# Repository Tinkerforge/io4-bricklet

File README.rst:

IO-4 Bricklet
=============

This repository contains the firmware source code and the hardware design
files. The documentation generator configs can be found at
https://github.com/Tinkerforge/generators

Repository Content
------------------

software/:
 * examples/: Examples for all supported languages
 * build/: Compiled files
 * src/: Source code of firmware
 * Makefile: Makefile to build project

hardware/:
 * Contains KiCad project files and additionally schematics as PDF

datasheets/:
 * Contains datasheets for sensors and complex ICs that are used

Hardware
--------

The hardware is designed with the open source EDA Suite KiCad
(http://www.kicad.org). Before you are able to open the files,
you have to install the Tinkerforge kicad-libraries
(https://github.com/Tinkerforge/kicad-libraries). You can either clone
them directly in hardware/ or clone them in a separate folder and
symlink them into hardware/
(ln -s kicad_path/kicad-libraries project_path/hardware). After that you
can open the .pro file in hardware/ with KiCad and from there view and
modify the schematics and the PCB layout.

Software
--------

If you want to do your own Brick/Bricklet firmware development we highly
recommend that you use our build environment setup script and read the
tutorial (https://www.tinkerforge.com/en/doc/Tutorials/Tutorial_Build_Environment/Tutorial.html).

To compile the C code we recommend you to install the newest GNU Arm Embedded
Toolchain (https://launchpad.net/gcc-arm-embedded/+download).
You also need to install bricklib (https://github.com/Tinkerforge/bricklib)
and brickletlib (https://github.com/Tinkerforge/brickletlib).

You can either clone it directly in software/src/ or clone it in a
separate folder and symlink it into software/src/
(ln -s bricklib_path/bricklib project_path/software/src/ and
ln -s brickletlib_path/brickletlib project_path/software/src/).
Finally make sure to have CMake installed
(http://www.cmake.org/cmake/resources/software.html).

After that you can build the firmware by invoking make in software/.
The firmware (.bin) can then be found in software/build/ and uploaded
with brickv (click button "Flashing" on start screen).

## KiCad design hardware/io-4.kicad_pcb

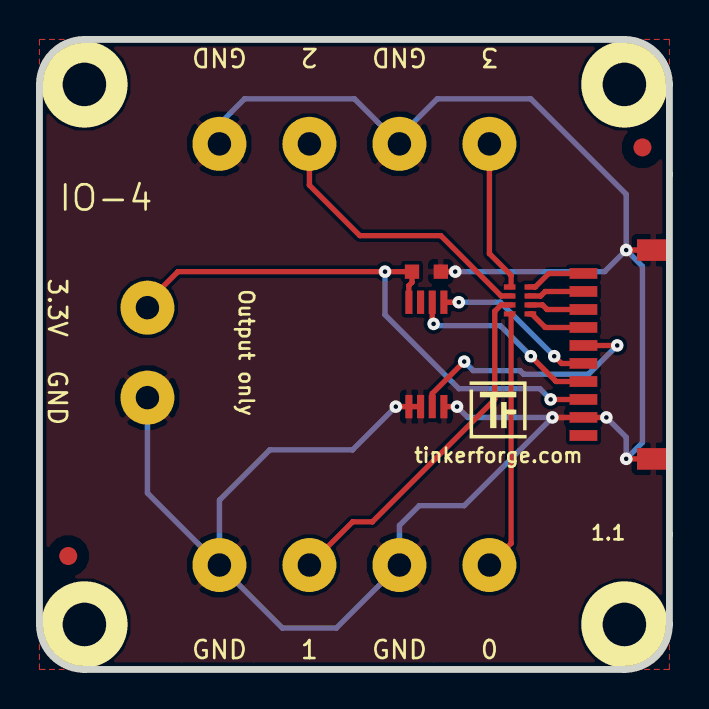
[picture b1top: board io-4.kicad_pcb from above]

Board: 2 copper layers, 35.0 x 35.0 mm, 18 parts (0 on the bottom side), 13 nets.

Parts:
C1: 100nF; C0603
Fiducial_Mark: VAL**; Fiducial_Mark
Fiducial_Mark#2: VAL**; Fiducial_Mark
J1, J2, J3, J4, J5: AKL_5_2
P1: CON-SENSOR
RP1: 100; 4X0402
Ref**: Val**; Logo_31x31
U1: M24C64; TSSOP8
U2, U3, U4, U5: DRILL; DRILL_NP
VAL: WEEE_7mm
VAL#2: CE_5mm

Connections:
GND: C1.2, J1.2, J2.2, J3.1, J4.1, J5.1, P1.2, P1.EP, U1.1, U1.2, U1.4
unnamed: J1.1, RP1.8
unnamed: J2.1, RP1.7
unnamed: J3.2, RP1.6
unnamed: J4.2, RP1.5
unnamed: P1.6, U1.3
unnamed: P1.7, RP1.1
unnamed: P1.8, RP1.2
unnamed: P1.9, RP1.3
unnamed: P1.10, RP1.4
SCL: P1.4, U1.6
SDA: P1.5, U1.5
VCC: C1.1, J5.2, P1.3, U1.8

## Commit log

2011-08-25 initial hardware source commit
2011-08-25 add project description
2011-09-13 add java bindings and examples
2011-09-14 limit line length of java examples to 100 characters
2011-09-23 Add C# examples and bindings
2011-09-23 Add C# bindings
2011-10-05 Remove Bindings and IP Connection (these are generated and they change too often) and rename bindings to examples
2011-10-05 add tinkerforge package to python imports
2011-10-06 remove faulty gcc commandline invocation
2011-10-06 add firmware version and name
2012-02-13 checkin of version V1.1 - remove address line resistor - add fiducials - new pcb layout - add protection resitors
2012-02-14 add compatability for different tick types
2012-02-14 calculation and message together in one tick task if necessary
2012-02-15 Add changelog
2012-02-15 Move software changelog to software folder
2012-04-25 Unify capitalization of "IP connection" in examples
2012-05-09 Add PHP examples
2012-05-14 java: Remove unnecessary new String(...) calls
2012-05-25 Add Ruby examples
2012-06-05 Fix register_callback syntax error in Ruby examples on Windows
2012-06-12 Use correct term 'Bricklet' in example code error message
2012-06-12 Prefer IPConnection destroy over join_thread
2012-07-01 Add generate_makefile.bat for windows
2012-07-23 Register callback before enabling interrupt in all examples
2012-07-25 Add Delphi examples
2012-08-01 Add monoflop functionality
2012-08-08 delphi: Add comment about UID
2012-09-07 Ignore temporary build files
2012-09-13 Reorder code and add _NOP(), otherwise gcc > 4.5 creates faulty firmware...
2012-10-04 Extend .gitignore
2012-10-24 Make cmake find the correct objcopy binary
    On some systems cmake uses the wrong objcopy binary, tell it to use
    the correct one.
2012-10-25 Increase version (there was a difference in firmware without version update)
2012-10-25 Update changelog
2012-10-26 Remove the now obsolete __NOP
    As the problem is fixed correctly now by enlarging the BrickContext
    from 250 to 256.
2012-11-13 Support for protocol 2.0
2012-11-29 Make examples compatible to Protocol V2.0
2012-11-29 Make Ruby examples Protocol 2.0 compatible
2012-11-29 Make C examples Protocol 2.0 compatible
2012-11-29 Make Java examples Protocol 2.0 compatible
2012-11-29 Make PHP examples Protocol 2.0 compatible
2012-11-30 Make Delphi examples protocol 2.0 compatible
2012-11-30 Add and fix invalid parameter checks
2012-11-30 delphi: Remove unnecessary parentheses and call destructor again
2012-12-05 Add protocol 2.0 compatability to C# bindings
2012-12-06 Fix C example
2012-12-11 Avoid g++ warnings about missing casts in C examples
2013-01-09 Use specific device object for callbacks
2013-01-14 Add possibility to set selected values to API
2013-01-17 Make Java examples compatible to new listener approach
2013-02-07 Use IPconnection disconnect explicitly in examples
2013-02-18 Add Visual Basic .NET examples
2013-08-12 Add shell examples
2013-08-14 shell: Explain magic number
2013-08-16 shell: Fix syntax error
2013-08-21 windows: Don't trigger a build in generate_makefile.bat
    Also use normal make instead of a special named one.
2013-08-28 Add edge counters for all pins
2014-01-10 Add Perl examples
2014-01-15 php: Use const for constant values
2014-02-07 Add Mathematica examples
2014-02-10 perl: fixed namespace
2014-02-12 javascript: add examples
2014-02-18 javascript: examples fixed
2014-02-20 javascript: add html examples
2014-02-24 javascript: port 4280, startExample()
2014-02-28 javascript: Break long lines and cleanup whitespace
2014-02-28 Fix typo
2014-03-05 Add LabVIEW examples
2014-03-06 labview: Add examples in LV2010 format
2014-03-26 matlab: add examples
2014-04-02 java: Unify constants style
2014-04-02 perl: Unify print style
2014-04-17 matlab: Adapt examples to new callback style
2014-04-17 matlab: Add parentheses to make pygments happy
2014-07-15 java: Replace System.console() usage with an Eclipse compatible pattern
2014-12-02 Use ReadLine instead of ReadKey for C# example
2015-02-13 vbnet: Use ReadLine instead of ReadKey
    Because ReadKey doesn't work with a pipe as stdin on the RED Brick.
2015-03-02 windows: Stop cmake from searching for mingw32-make.exe
    Using MinGW Makefiles as generator makes cmake search for mingw32-make.exe
    which might not be installed because GnuWin32's make.exe is used instead.
2015-03-26 checkin of current hardware files
2015-04-09 c: Whitespace
2015-06-24 javascript: Clean up output creation
2015-06-29 octave: Handle short difference between Octave 3.6 and 3.8
    In Octave 3.6 a short is not automatically handled as a number.
2015-07-23 Make JavaScript browser example textarea readonly
2015-07-27 Cleanup C/C++, C#, Java, Python and Ruby examples
2015-07-29 Reformat changelog
2015-08-07 Use full device class name in Python examples
2015-08-12 Fix minor warnings in C/C++ examples
2015-08-14 Cleanup Delphi examples
2015-08-18 Cleanup VB.NET examples
2015-08-19 Cleanup Perl examples
2015-09-09 Duplicate cmake call to fix bug during cmake creation
2015-09-18 Generator based example cleanup
2015-09-30 Add simple input mode example
2015-09-30 Improve callback handling in shell example
2015-11-12 matlab: Fix callback handling for R2014a
    http://undocumentedmatlab.com/blog/matlab-callbacks-for-java-events-in-r2014a
2015-11-25 Include date and commit into changelog
2015-11-30 vbnet: Break long line
2016-05-18 c: Add missing device destroy call
2016-06-29 Whitespace
2016-07-01 Make the change UID comment more explicit
2017-04-13 csharp: Adapt example
2017-04-20 shell: Adapt example
2017-06-02 octave: Use javaObject instead of deprecated java_new
2017-08-01 Add 3d information (final)
2017-08-01 Convert *.brd to *.kicad_pcb
2017-08-01 Add 3d model (*.step & *.FCStd)
2017-11-30 Update examples from generator
2017-12-07 mathematica: Also generate .nb files
2018-01-26 c: Fine-tune printf format
2018-02-19 javascript: Close div tag correctly
2018-02-20 Cleanup KiCad libraries config
    Ensure LibDir=kicad-libraries and LibName1=tinkerforge.
    Remove special library.
2018-05-11 Rename files
2018-05-24 perl: Use strict in examples
2018-07-11 Add Makefile with docker support
2018-07-11 Update directory structure and build instructions
2018-07-11 Remove obsolete generate_makefile scripts
2018-11-06 Add rust examples
2018-11-07 rust: Accept host names for ip connection, fix naming inconsistencies
2018-11-07 rust: Rename callback receivers.
2018-12-14 Add go examples.
2018-12-18 go: Change import path.
2018-12-18 go: Change import path again.
2018-12-20 rust: Reformat examples.
2019-01-24 mqtt: Add examples.
2019-01-24 mqtt: Fix example header.
2019-01-24 mqtt: Remove executable bit in example permissions.
2019-01-24 go: Minor example fixes.
2019-01-24 mqtt: Minor example fixes.
2019-03-28 mqtt: Fix whitespace.
2019-08-22 c: Adapt to bindings changes
2020-01-13 examples: Use python3 input instead of python2 raw_input.
2020-01-13 examples: mqtt: Remove trailing whitespace.
2020-04-07 examples: rust: Always block when calling bindings functions.
2021-10-25 Update KiCad link
    https://www.kicad.org/blog/2021/10/Avoid-links-to-former-kicad-domain/
2022-07-06 Add license files.

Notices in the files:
hardware/io-4.kicad_pcb:
Licensed under CERN OHL v.1.1
Copyright (©) 2011, B.Nordmeyer
Copyright Tinkerforge GmbH 2011.
This documentation describes Open Hardware and is licensed under the
CERN OHL v. 1.1.
